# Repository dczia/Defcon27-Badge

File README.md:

# Defcon27-Badge

```
 ____   ____ ______             ____   ____ ____ _____
|  _ \ / ___|__  (_) __ _      |  _ \ / ___|___ \___  |
| | | | |     / /| |/ _` |_____| | | | |     __) | / /
| |_| | |___ / /_| | (_| |_____| |_| | |___ / __/ / /
|____/ \____/____|_|\__,_|     |____/ \____|_____/_/
```

# Lazer Theramin Synth Badge

This year we wanted to do something different. Our idea is to use two laser time of flight sensors that can measure the distance of your hands moving around infront of the badge to control a synthesizer to create a laser theremin.

- 64Mhz Arm CortexM4F with Bluetooth 5
- 5 Mechanical Clicky Low Profile Key Switches
- Rotary Encoder with Click Button
- OLED Display
- Onboard Speaker and Amplifier!
- 1/8" Headphone Out Audio Jack
- SD Card Storage
- RGB Leds
- 2 SAO / "Shitty Add-On" Connectors

# Hardware Detail

- Rigado BMD-340 aka NRF52 Microconroller
  - Bluetooth, Lots of IO's, Fast, Small, Low Power, and cheap ~ $12
  - https://www.rigado.com/products/modules/bmd-340/

- Laser Time of Flight Sensors - Dev modules are from Adafruit 
  - https://www.adafruit.com/product/3317

- DAC / Amplifier - mediumRehr Audio™

- Speaker - Oval 1watt onboard speaker

- Buttons - Kalih Low Profile White Clicky Keyswitches. Oh yeah. This is the shit right here.
  - https://novelkeys.xyz/collections/switches/products/kailh-low-profile-switches

- Keycaps - Note, the low profile caps are for the Kalih low profile switches only. 
  - https://novelkeys.xyz/collections/keycaps/products/kailh-low-profile-keycaps-blank
  
- LEDs
  - Neopixel RGB

- Screen - SSD1306 OLED

- SD Card

# Software

- Environment is GNU ARM GCC with your choice of IDE

- Programming can be done via a J-Link Segger or by SD Card (coming soon)

- Uses Nordic SoftDevice version XXX

- See [EnvironmentSetup](Software/EnvironmentSetup.md) for more info

# Board

- Designed in KiCad

# Documentation

- [Board Build Guide](BuildGuide.md)
- [EnvironmentSetup](Software/EnvironmentSetup.md)

# Links to relevant information

- [Documentation library - nordicsemi.com](https://www.nordicsemi.com/DocLib)

- DC801 Party Badge - Good source for setting up dev env, and seeing some Rigado code in action - https://github.com/DC801/DC26PartyBadge

- oxvox - Rigado based pwm synth - https://github.com/mediumrehr/oxvox

- Basic audio synthesis with an Arduino - https://makezine.com/projects/make-35/advanced-arduino-sound-synthesis/

- mintysynth - simple arduino synth - https://mintysynth.com/

- Nordic PWM Driver info: https://infocenter.nordicsemi.com/index.jsp?topic=%2Fcom.nordic.infocenter.sdk5.v15.3.0%2Fhardware_driver_pwm.html&cp=5_1_2_0_8

- PWM Primer - https://provideyourown.com/2011/analogwrite-convert-pwm-to-voltage/

# Devboard pinout

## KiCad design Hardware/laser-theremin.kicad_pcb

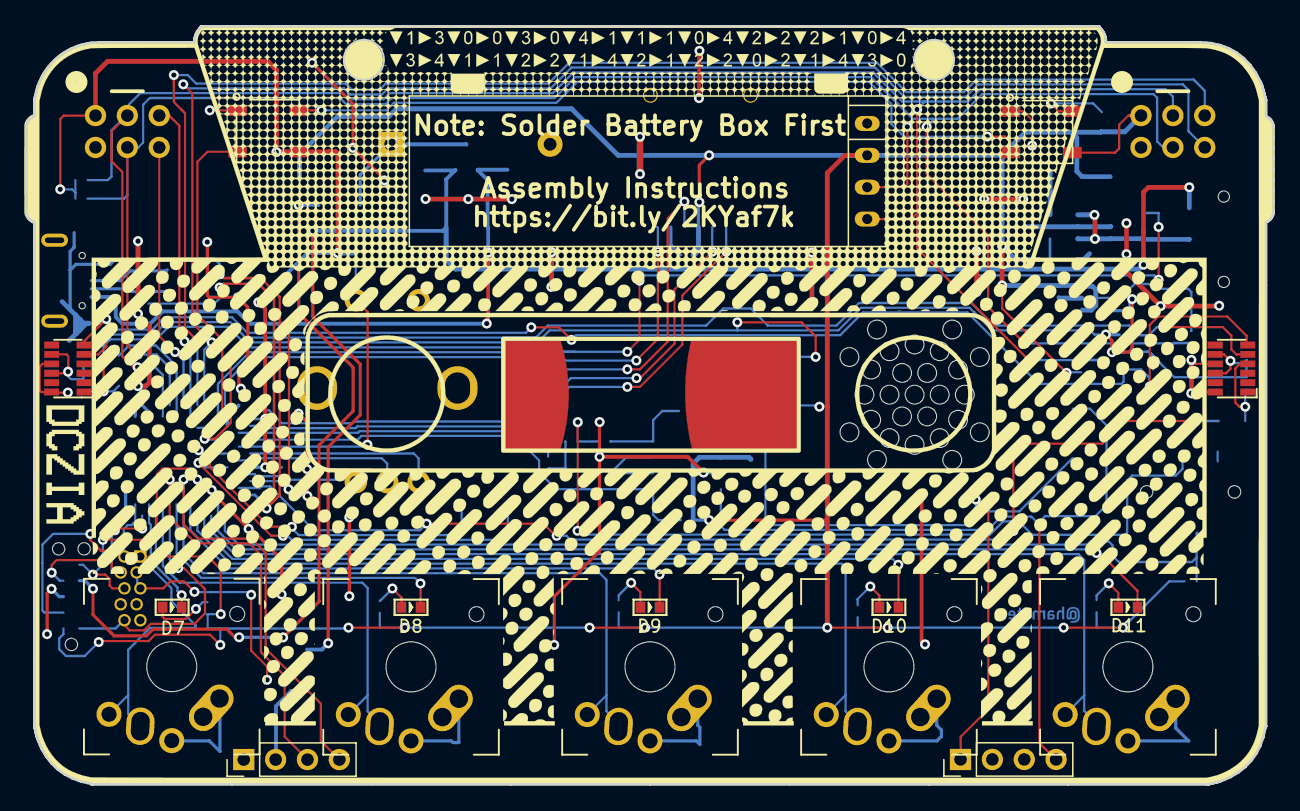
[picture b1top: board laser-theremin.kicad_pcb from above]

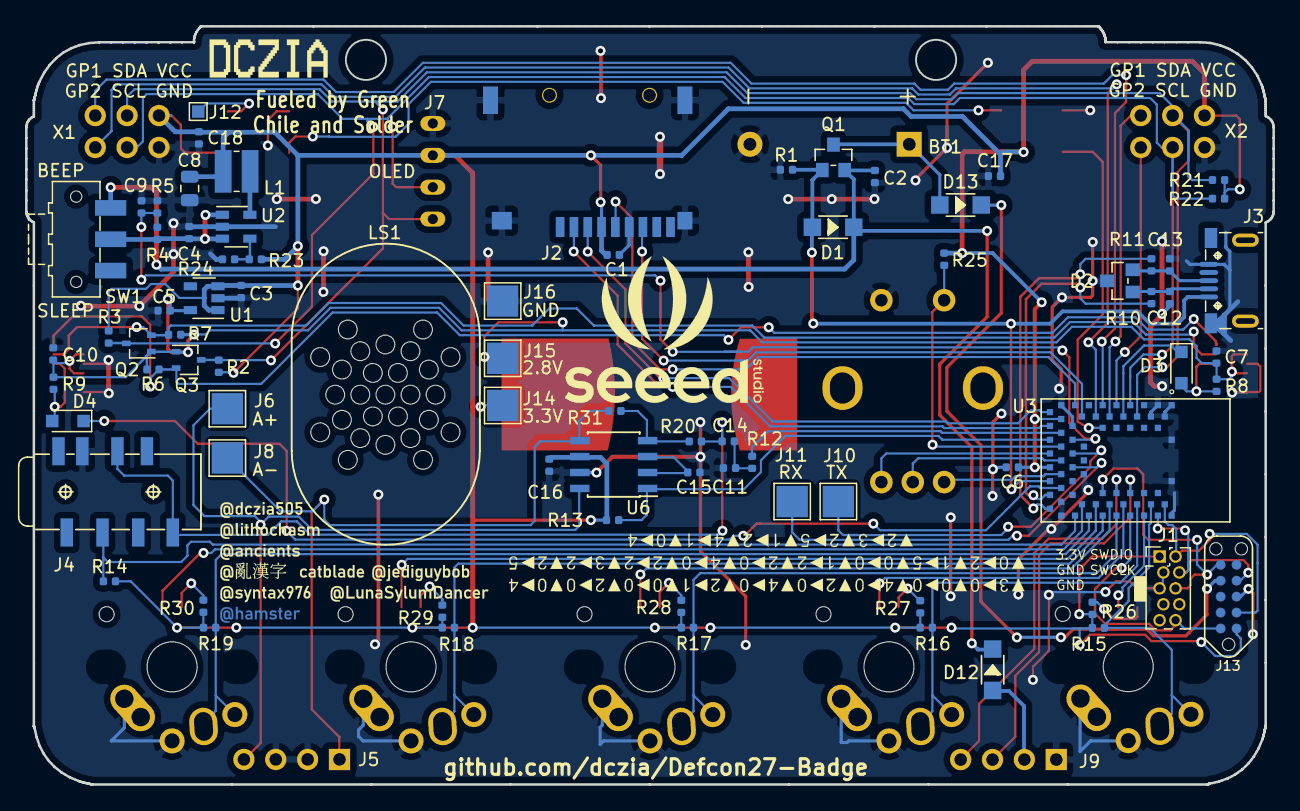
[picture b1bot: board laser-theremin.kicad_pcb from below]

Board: 2 copper layers, 99.4 x 60.4 mm, 99 parts (79 on the bottom side), 71 nets.

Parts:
BT1: Battery; BatteryHolder_Keystone_2479_3xAAA-NoDrill
C1, C2, C7, C10, C16, C17, C18: 0.1uF; C_0402_1005Metric
C3, C5, C15: 1uF; C_0402_1005Metric
C4, C6: 4.7uF; C_0402_1005Metric
C8: 22uF; C_0805_2012Metric
C9: 1nF; C_0402_1005Metric
C11: 10nF; C_0402_1005Metric
C12, C13: 47pF; C_0402_1005Metric
C14: 0.33uF; C_0402_1005Metric
D1, D12, D13: D_Schottky; SOD-123
D2: SP0503BAHT; SOT-23
D3, D4: 1N4148; D_SOD-323_HandSoldering
D5, D6: SK6812; LED4-SMD-5050
D7, D8, D9, D10, D11: LED; LED-0603
J1: JTAG; PinHeader_2x05_P1.27mm_Vertical_Sneaky
J2: Micro_SD_Card_SPI; MicroSD-Socket-Seeed-320090008
J3: USB_B_Micro; MICRO-USB5+4P-SMD-0.65-B
J4: Audio Out; AUDIO8P-SMD-3.5-14.5X6X5MM
J5: Rack2; PinHeader_1x04_P2.54mm_Vertical
J6, J8, J10, J11, J14, J15, J16: Conn_01x01; TestPoint_Pad_2.5x2.5mm
J7: OLED
J9: Rack1; PinHeader_1x04_P2.54mm_Vertical
J12: Conn_01x01; TestPoint_Pad_1.0x1.0mm
J13: TagConnect; TC2050-NL_SMALL
L1: 4.7uH; L_Wuerth_MAPI-3020
LS1: Speaker
Q1: FDN360P; SOT-23
Q2, Q3: BSS138; SOT-323_SC-70
R1, R2, R3, R6, R7, R13, R14, R15, R16, R17, R18, R19, R25: 10k; R_0402_1005Metric
R4: 806k; R_0402_1005Metric
R5: 2M; R_0402_1005Metric
R8, R9: 47k; R_0402_1005Metric
R10, R11: 27R; R_0402_1005Metric
R12: 1k; R_0402_1005Metric
R20, R31: 20k; R_0402_1005Metric
R21, R22: 4.7k; R_0402_1005Metric
R23: 540k; R_0402_1005Metric
R24: 120k; R_0402_1005Metric
R26, R27, R28, R29, R30: 33R; R_0402_1005Metric
SW1: Power; SW_SPDT_CK-JS102011SAQN
SW2, SW3, SW4, SW5, SW6: SW_Push; MX-Alps-Choc-1U
SW7: Volume; RotaryEncoder
U1: XC6221A282MR-G; SOT-23-5
U2: PAM2305DABADJ; SOT-23-5
U3: BMD-340; RIGADO_BMD-340
U4, U5: VL6180X
U6: LM4861; SOIC-8_3.9x4.9mm_P1.27mm
X1, X2: Badgelife_sao_connector_v169bis; Badgelife-Shitty-v1.69bis

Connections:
+2V8: C5.1, C7.1, C10.1, J15.1, Q2.1, Q3.1, R6.2, R7.2, R8.2, R9.2, U1.5, U4.8, U4.10, U5.8, U5.10
+3V3: C1.2, C3.1, C6.1, C8.1, C16.1, C17.2, C18.2, D5.3, D6.3, J1.1, J2.4, J7.2, J13.1, J14.1, L1.2, R2.2, R3.2, R13.2, R14.2, R15.1, R16.1, R17.1, R18.1, R19.1, R21.2, R22.2, R23.2, R25.1, R26.1, R27.1, R28.1, R29.1, R30.1, U1.1, U1.3, U3.17, U3.65, U6.6, X1.1, X2.1
+BATT: BT1.1, D13.2, Q1.3
+BATT_SW: C4.1, R4.2, SW1.2, U2.1, U2.3
/LED Driver/DOUT: D6.4, J12.1
/USB+: R11.2, U3.68
/USB-: R10.2, U3.67
A+: J5.4, J6.1, U6.8
A-: J5.1, J8.1, R31.2, U6.5
AUDIO_SHTDN: R13.1, U3.63, U6.1
CV: J9.3, U3.58
DIN: D5.2, U3.52
ENC_A: SW7.A, U3.25
ENC_B: SW7.B, U3.64
ENC_C: SW7.C, U3.23
ENC_SW: R25.2, SW7.S1, U3.21
GATE: J9.4, U3.57
GND: BT1.2, C1.1, C2.2, C3.2, C4.2, C5.2, C6.2, C7.2, C8.2, C9.2, C10.2, C11.2, C12.1, C13.2, C15.1, C16.2, C17.1, C18.1, D2.3, D5.1, D6.1, J1.3, J1.5, J2.6, J2.10, J3.5, J3.6, J4.2, J5.2, J5.3, J7.1, J9.1, J13.3, J16.1, R1.1, R5.1, R24.1, SW2.2, SW3.2, SW4.2, SW5.2, SW6.2, SW7.S2, U1.2, U2.2, U3.1, U3.2, U3.3, U3.4, U3.5, U3.16, U3.18, U3.29, U3.30, U3.45, U3.46, U3.47, U3.55, U4.9, U4.12, U5.9, U5.12, U6.7, X1.2, X2.2
HP_DETECT: J4.6, R14.1, U3.31
KEY_A: R19.2, SW6.1, U3.33
KEY_C: R16.2, SW3.1, U3.40
KEY_D: R15.2, SW2.1, U3.42
KEY_I: R18.2, SW5.1, U3.35
KEY_Z: R17.2, SW4.1, U3.37
LED_A: D11.1, U3.32
LED_C: D8.1, U3.38
LED_D: D7.1, U3.41
LED_I: D10.1, U3.34
LED_Z: D9.1, U3.36
MISO0: J2.7, U3.14
MOSI0: J2.3, U3.61
unnamed: C11.1, C14.1, R12.1
unnamed: C12.2, D2.1, J3.2, R10.1
unnamed: C13.1, D2.2, J3.3, R11.1
unnamed: C14.2, J4.3, J4.4, R20.1
unnamed: C15.2, U6.2, U6.3
unnamed: D3.2, R8.1, U4.4
unnamed: D4.2, R9.1, U5.4
unnamed: D5.4, D6.2
unnamed: D7.2, R26.2
unnamed: D8.2, R27.2
unnamed: D9.2, R28.2
unnamed: D10.2, R29.2
unnamed: D11.2, R30.2
unnamed: D12.2, J9.2
unnamed: D13.1, J13.7
unnamed: J10.1, U3.22
unnamed: J11.1, U3.24
unnamed: L1.1, U2.5
unnamed: R20.2, R31.1, U6.4
unnamed: R23.1, R24.2, U2.4
PWM_IN: R12.2, U3.19
RACK_PWR: C2.1, D1.1, D12.1, Q1.2, SW1.1
S1_1: U3.11, X1.5
S1_2: U3.12, X1.6
S2_1: U3.10, X2.5
S2_2: U3.9, X2.6
SCK0: J2.5, U3.15
SCL: J7.3, Q2.3, R3.1, R22.1, U3.7, X1.4, X2.4
SCL_2_8: Q2.2, R7.1, U4.5, U5.5
SDA: J7.4, Q3.3, R2.1, R21.1, U3.6, X1.3, X2.3
SDA_2_8: Q3.2, R6.1, U4.6, U5.6
SD_CS: J2.2, U3.62
SW0: J1.6, J13.6, U3.56
SWCLK: J1.4, J13.4, U3.43
SWDIO: J1.2, J13.2, U3.44
TOF1_SHDN: D4.1, U3.27
TOF2_SHDN: D3.1, U3.8
VBAT_SENSE: C9.1, R4.1, R5.2, U3.20
VBUS: D1.2, J3.1, Q1.1, R1.2, U3.66
nRESET: J1.10, J13.10, U3.39

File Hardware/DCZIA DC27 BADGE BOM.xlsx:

Refdes | Manufacturer | Part Number | Seeed OPL | Other supplier | Description | Package | Cost Each (assumes 100 unit pricing) | Qty per board | Stuff? | QOH | Needed | To Order | Cost Per Board | Qty ordered | Actual Cost | Supplier |  | Seeed OPL
To Stuff Later
BT1 |  |  |  | https://www.aliexpress.com/item/32323069094.html?spm=a2g0s.9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 | 3xAAA Battery Box |  | 0.28000000000000003 | 1 |  |  |  |  | 0.28000000000000003
SW2,SW3,SW4,SW5,SW6 |  | Kaihl Switches |  |  |  |  | 0.66 | 5 |  |  |  |  | 3.3000000000000003
LS1 |  |  |  | https://www.aliexpress.com/item/20pcs-lot-Acoustic-Speaker-2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 | Speaker, 24x15mm |  | 0.33 | 1 |  |  |  |  | 0.33
OLED |  |  |  |  | OLED display
Virtual, Non-stuff
J1 |  |  |  |  | 2x10 1.27 header, JTAG |  |  |  | N |  |  |  | 0
J5,J9 |  |  |  |  | Rack |  |  |  | N
J7 |  |  |  |  | OLED connector |  |  |  | N
J13 |  |  |  |  | TagConnect |  |  |  | N
J6,J8,J10,J11,J12 |  |  |  |  | Test points |  |  |  | N
X1,X2 |  |  |  |  | SAO 1.69bis |  |  |  | N |  |  |  | 0
R21,R22 |  |  | RC0402JR-074K7L |  | 4.7k DNS | 0402 | 8.0000000000000004E-4 | 2 |  |  |  |  | 1.6000000000000001E-3
SW7 |  |  | 311130001 |  | Rotary encoder, 12mm DNS |  | 0.61 | 1 |  | m |  |  | 0.61
Stuff at Fab
C1,C2,C7,C10,C16,C17,C18 |  |  | 302010024 |  | 0.1uF Cap | 0402 | 0.01 | 12 |  |  |  |  | 0.12
C3,C5,C15 |  |  | 302010003 |  | 1uF | 0402 | 0.01 | 3 |  |  |  |  | 0.03
C4,C6 |  |  | 302010019 |  | 4.7uF | 0402 | 0.01 | 2 |  |  |  |  | 0.02
C8 |  |  | 302010171 |  | 22uF | 0805 | 2.4E-2 | 1 |  | m |  |  | 2.4E-2
C9 |  |  | 302010005 |  | 1nF | 0402 | 0.01 | 1 |  |  |  |  | 0.01
C11 |  |  | 302010006 |  | 10nF | 0402 | 0.01 | 1 |  |  |  |  | 0.01
C12,C13 |  |  | 302010007 |  | 47pf | 0402 | 0.01 | 2 |  |  |  |  | 0.02
C14 |  |  | CL05A334KQ5NNNC |  | 0.33uF | 0402 | 1.15E-2 | 1 |  | m |  |  | 1.15E-2
D1,D12,D13 |  | B5819W | 304020034 |  | Schottky | SOD-123 | 2.3E-2 | 1 |  |  |  |  | 2.3E-2
D2 |  | CESD5V0AP | 304050003 |  | TVS diode | SOT-23 | 3.2000000000000001E-2 | 1 |  | skip |  |  | 3.2000000000000001E-2
D3,D4 |  | 1N4148 | 1N4148WS |  | General purpose diode | SOD-323 | 1.49E-2 | 2 |  |  |  |  | 2.98E-2
D7,D8,D9,D10,D11 |  |  | 19-217/R6C-AL1M2VY/3T |  | Red LED | 0603 | 2.3199999999999998E-2 | 5 |  | m |  |  | 0.11599999999999999
J2 |  | TF-01 | 320090008 |  | MicroSD socket |  | 0.109 | 1 |  |  |  |  | 0.109
J3 |  |  | 320010000 |  | USB micro, 'with holes' |  | 0.11799999999999999 | 1 |  | m |  |  | 0.11799999999999999
J4 |  |  | 320040003 |  | Headphone jack |  | 0.185 | 1 |  |  |  |  | 0.185
L1 |  |  | 303010114 |  | 4.7uH inductor | 3x2.1mm | 4.4999999999999998E-2 | 1 |  |  |  |  | 4.4999999999999998E-2
Q1 |  | NCE3407A | 305030010 | FDN360P | P-channel mosfet | SOT-23 | 4.7E-2 | 1 |  |  |  |  | 4.7E-2
Q2,Q3 |  | BSS138 | 305030000 |  | N-ch mosfet | SOT-323 | 3.3000000000000002E-2 | 2 |  |  |  |  | 6.6000000000000003E-2
R1,R2,R3,R6,R7,R13,R14,R15,R16,R17,R18,R19,R25 |  |  | RC0402JR-0710KL |  | 10k | 0402 | 6.9999999999999999E-4 | 10 |  |  |  |  | 7.0000000000000001E-3
R4 |  |  | 0402WGF8063TCE |  | 806k | 0402 | 1.2999999999999999E-3 | 1 |  |  |  |  | 1.2999999999999999E-3
R5 |  |  | RC0402JR-072ML |  | 2M | 0402 | 1.2999999999999999E-3 | 1 |  |  |  |  | 1.2999999999999999E-3
R8,R9 |  |  | RC0402FR-0747KL |  | 47k | 0402 | 8.9999999999999998E-4 | 2 |  |  |  |  | 1.8E-3
R10,R11 |  |  | RC0402FR-0727RL |  | 27R | 0402 | 1.5E-3 | 2 |  |  |  |  | 3.0000000000000001E-3
R12 |  |  | RC0402JR-071KL |  | 1k | 0402 | 1.6999999999999999E-3 | 1 |  |  |  |  | 1.6999999999999999E-3
R23 |  |  | RC0402FR-07536KL |  | 536k 1% | 0402 | 5.9999999999999995E-4 | 1 |  |  |  |  | 5.9999999999999995E-4
R24 |  |  | 0402WGJ0124TCE |  | 120k 1% | 0402 | 6.9999999999999999E-4 | 1 |  |  |  |  | 6.9999999999999999E-4
R26,R27,R28,R29,R30 |  |  | RC0402FR-0733RL |  | 33R | 0402 | 1.6000000000000001E-3 | 5
R20,R31 |  |  | RC0402JR-0720KL |  | 20k | 0402 | 8.0000000000000004E-4 | 2
U1 |  | XC6221A282MR-G | XC6221A282MR-G |  | 2.8v vreg | SOT-25 | 8.4099999999999994E-2 | 1 |  | m |  |  | 8.4099999999999994E-2
U2 |  | PAM2305DABADJ | PAM2305AABADJ |  | 3.3 buck vreg | SOT-23-5 | 0.13159999999999999 | 1 |  |  |  |  | 0.13159999999999999
D5,D6 |  | SK6812 |  |  |  |  |  |  |  | skip
SW1 |  | JS102011SAQN |  | Digikey 401-1999-1-ND Mouser 611-JS102011SAQN |  |  | 0.48010000000000003 | 1 |  | skip |  |  | 0.48010000000000003
U3 |  | BMD-340 |  | On hand |  |  | 8 | 1 |  | m |  |  | 8
U4,U5 |  | VL6180X |  | Digikey 497-14702-1-ND Mouser 511-VL6180XV0NR/1 |  |  | 3.7471999999999999 | 2 |  | m |  |  | 7.4943999999999997
U6 |  | LM4861 |  | Digikey 296-38566-1-ND Mouser 926-LM4861MX/NOPB |  | SOIC-8 | 0.93810000000000004 | 1 |  |  |  |  | 0.93810000000000004
 |  |  |  |  |  |  |  |  |  |  |  | Total | 22.683599999999995
 |  |  |  |  |  |  |  |  |  |  | 75 | Boards | 114.21 | 1.5227999999999999
 |  |  |  |  |  |  |  |  |  |  |  | PCBA Cost | 1794 | 23.92
 |  |  |  |  |  |  |  |  |  |  | 0.93 | audio | 69.75
 |  |  |  |  |  |  |  |  |  |  | 7.4943999999999997 | laser | 562.07999999999993
 |  |  |  |  |  |  |  |  |  |  | 7 | bmd340 | 525
 |  |  |  |  |  |  |  |  |  |  | 1 | batteries | 75
 |  |  |  |  |  |  |  |  |  |  | 0.5 | batt box | 37.5
 |  |  |  |  |  |  |  |  |  |  | 3.25 | Keys | 243.75
 |  |  |  |  |  |  |  |  |  |  |  | Total | 3421.29 | 45.617199999999997

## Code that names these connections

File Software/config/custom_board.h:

/**
 *
 * @file custom_board.h
 *
 * @date June 15 2019
 * @author hamster
 *
 * This is the custom board defines for the LEDs and etc
 *
 */

#ifndef DCZIA_H
#define DCZIA_H

// Setting to zero disables the Nordic initializers
#define LEDS_NUMBER    		0
#define BUTTONS_NUMBER      0


/***
 *      _     _____ ____
 *     | |   | ____|  _ \ ___
 *     | |   |  _| | | | / __|
 *     | |___| |___| |_| \__ \
 *     |_____|_____|____/|___/
 *
 */
#define LED_D_PIN     	23
#define LED_C_PIN       20
#define LED_Z_PIN       21
#define LED_I_PIN       16
#define LED_A_PIN       14

/***
 *      ____        _   _
 *     | __ ) _   _| |_| |_ ___  _ __  ___
 *     |  _ \| | | | __| __/ _ \| '_ \/ __|
 *     | |_) | |_| | |_| || (_) | | | \__ \
 *     |____/ \__,_|\__|\__\___/|_| |_|___/
 *
 */
#define BUTTON_D_PIN    24
#define BUTTON_C_PIN    22
#define BUTTON_Z_PIN    19
#define BUTTON_I_PIN    17
#define BUTTON_A_PIN    15
#define ENC_SW_PIN      5
#define ENC_A_PIN       9
#define ENC_B_PIN       (32 + 15)
#define ENC_C_PIN       7

#define BUTTON_PRESSED 	        0
#define BUTTONS_ACTIVE_STATE    0

/***
 *      _   _   _    ____ _____
 *     | | | | / \  |  _ \_   _|
 *     | | | |/ _ \ | |_) || |
 *     | |_| / ___ \|  _ < | |
 *      \___/_/   \_\_| \_\|_|
 *
 */
#define RX_PIN          6
#define TX_PIN          8
#define CTS_PIN         NRF_UART_PSEL_DISCONNECTED
#define RTS_PIN         NRF_UART_PSEL_DISCONNECTED
#define HWFC           false

/***
 *      _ ____
 *     (_)___ \ ___
 *     | | __) / __|
 *     | |/ __/ (__
 *     |_|_____\___|
 *
 */
#define I2C_SDA_PIN     25
#define I2C_SCL_PIN     26

/***
 *      ____  ____ ___
 *     / ___||  _ \_ _|
 *     \___ \| |_) | |
 *      ___) |  __/| |
 *     |____/|_|  |___|
 *
 */
#define SPI_MISO_PIN    1
#define SPI_SCK_PIN     2
#define SPI_MOSI_PIN    (32 + 12)
#define SPI_SD_CS_PIN   (32 + 13)

/***
 *      ____                          ____
 *     |  _ \ __ _ _ __   __ _  ___  / ___|  ___ _ __  ___  ___  _ __
 *     | |_) / _` | '_ \ / _` |/ _ \ \___ \ / _ \ '_ \/ __|/ _ \| '__|
 *     |  _ < (_| | | | | (_| |  __/  ___) |  __/ | | \__ \ (_) | |
 *     |_| \_\__,_|_| |_|\__, |\___| |____/ \___|_| |_|___/\___/|_|
 *                       |___/
 */
#define TOF1_SHUTDOWN_PIN   11
#define TOF2_SHUTDOWN_PIN   27

/***
 *         _             _ _
 *        / \  _   _  __| (_) ___
 *       / _ \| | | |/ _` | |/ _ \
 *      / ___ \ |_| | (_| | | (_) |
 *     /_/   \_\__,_|\__,_|_|\___/
 *
 */
#define AUDIO_SHUTDOWN_PIN  (32 + 14)
#define AUDIO_HP_DETECT_PIN 13
#define AUDIO_PWM_PIN       3

/***
 *      ____  _          _
 *     |  _ \(_)_  _____| |___
 *     | |_) | \ \/ / _ \ / __|
 *     |  __/| |>  <  __/ \__ \
 *     |_|   |_/_/\_\___|_|___/
 *
 */
#define PIXELS_DOUT_PIN   (32 + 9)

/***
 *      ____  _           _
 *     |  _ \(_)___ _ __ | | __ _ _   _
 *     | | | | / __| '_ \| |/ _` | | | |
 *     | |_| | \__ \ |_) | | (_| | |_| |
 *     |____/|_|___/ .__/|_|\__,_|\__, |
 *                 |_|            |___/
 */
// It's a 128x32 OLED display with a SSD1306 driver
#define SSD1306_128_32

/***
 *     __     __
 *     \ \   / /__  ___ _ __  ___  ___
 *      \ \ / / __|/ _ \ '_ \/ __|/ _ \
 *       \ V /\__ \  __/ | | \__ \  __/
 *        \_/ |___/\___|_| |_|___/\___|
 *
 */
#define VOLTAGE_SENSE_PIN		NRF_SAADC_INPUT_AIN2    // P0.04

//// Clock
//// Low frequency clock source to be used by the SoftDevice
//// We're using the internal RC osc
/*#define NRF_CLOCK_LFCLKSRC      {.source        = NRF_CLOCK_LF_SRC_RC, \
                                 .rc_ctiv       = 16, \
                                 .rc_temp_ctiv  = 2, \
                                 .xtal_accuracy = NRF_CLOCK_LF_XTAL_ACCURACY_20_PPM} */



#endif // DCZIA_H

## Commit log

2019-03-12 Added Devboard Code
2019-03-12 Fixed makefile issue
2019-03-12 Update README.md
    Fixed some formatting issues
2019-03-12 Cleanup
2019-03-12 Update EnvironmentSetup.md
    Added some build env steps, need to complete.
2019-03-12 Update EnvironmentSetup.md
    Added stuffs
2019-03-12 Split up some stuff
2019-03-25 Added new stuf
2019-03-26 Added basis for PWM sdk code
2019-03-26 Fixed led code, removed some pwm stuff to get build working
2019-03-26 fixing stuff
2019-03-26 IT BEEEPSgit add ../../.! Speaker on pin 3
2019-03-26 Deleted some old code, cleaned up beep sounds
2019-03-26 Cleaned extra gitignore
2019-03-26 Added PWM Driver Code, changed makefile and sdk.h
2019-05-15 Add hardware design files
2019-06-03 Adding design files and outputs for proto1 and proto2
2019-06-10 Update README.md
    Cleaned up readme
2019-06-18 Updating design to final
2019-06-19 Updated reeeedddmeee
2019-06-21 Create BuildGuide
2019-06-21 Rename BuildGuide to BuildGuide.md
2019-06-22 Adding and updating code to support the prototype board at a base level More work to be done here, but this gets things started
2019-06-22 Changed readme to reflect right badge group
2019-06-25 Update README.md
    Fix Env setup link
2019-06-29 add PWM functionality
2019-07-03 add timer support. add support for distance sensors controlling frequency and amplitude
2019-07-07 fix pwm count bug to go all the way; increase timer and pwm speeds; change pwm and timer to control audio instead of LEDs
2019-07-08 rewrite button detect to support simultaneous presses
2019-07-10 Updated rough draft of build guide
2019-07-12 Updated build guide instuctions
2019-07-16 Fixed some build guide formatting
2019-07-21 Docker Build
    Made a docker file
    Made adjustments to makefile so it can build by default
2019-07-21 Mixed tabs/spaces and trailing spaces fix
2019-07-21 Update Makefile
    Fixed makefile
2019-07-21 Add dockerfile symlink
2019-07-22 Added User Manual
2019-07-24 Create/Publush .hex file in docker
2019-07-25 Cleanup main function and pull stuff into functions
2019-07-28 added LED theramin mode
2019-07-29 Lighting slowing coming together. Fixed A led issue
2019-07-31 Add E1M1 sequence.
2019-08-01 add encoder support and make buttons interrupt driven
2019-08-01 Added neopixel color modes
2019-08-02 Added light modes 1,2 &3 will add party mode later
2019-08-02 Extended boot sequence
2019-08-02 Fix formatting using cpplint to check
2019-08-02 Add bitmap method of setting LEDs
2019-08-02 Move Neopixel init out of boot sequence
2019-08-02 Pull OLED init stuff out of boot sequence and into a function
2019-08-02 Reduce led_mode 3 size
2019-08-02 Simplify boot sequence with bitmap mode
2019-08-03 restructure doom playback to use interrupts
2019-08-03 remove old doom music code
2019-08-03 add short debounce for buttons
2019-08-03 clean up menus and display
2019-08-03 cleaned up some light modes 👾
2019-08-03 add new waveforms selected by buttons
2019-08-04 add DCZia logo to boot screen
2019-08-04 add waveform visual on display
2019-08-04 add ability to change octave with encoder
2019-08-05 Adding support for theremini SAO remote keyboard
2019-08-06 Update BLE Name so it is readable in scanners. Removed one of the (many) printf buffer overflows for the name.
2019-08-06 Adding bootloader Adding uf2 converter
2019-08-06 Adding bootloader flash target
2019-08-07 Adding the final uf2 image
2019-08-08 Added ligt mode fixes
2019-08-09 Added build images
2019-08-09 Update BuildGuide.md
    Added images
2019-08-09 Compressed images
